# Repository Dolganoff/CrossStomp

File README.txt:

Copyright Alexei Dolganov (http://www.dolganoff.com)

Definitions
-----------

Here, "Documentation" means schematic diagrams, designs, circuit or circuit
board layouts, mechanical drawings, flow charts and descriptive text,
and other explanatory material.

Legal stuff
-----------

This documentation describes Open Hardware product and is licensed under the
CERN OHL 1.2 (see files LICENSE and cern_ohl_v_1_2_howto-1.pdf for more details 
on designs usage and redistribution.

You may redistribute and modify this documentation under the terms of the
CERN OHL 1.2. (http://ohwr.org/cernohl). 

This documentation is distributed WITHOUT ANY EXPRESS OR IMPLIED WARRANTY, 
INCLUDING OF MERCHANTABILITY, SATISFACTORY QUALITY AND FITNESS FOR A 
PARTICULAR PURPOSE. Please see the CERN OHL v.1.2 for applicable conditions.

You're allowed to use this documentation for free and to build the described 
product and even commercialise it **as long as you comply with the license**.
You must redistribute the documentaion with your product under the same
license terms. 

Notification
------------

You're not obliged to do so but I ask you to let me know if you're building
described product for your own use or commercialise it. 

Software tools used in this project:
------------------------------------

* LTSpice (http://www.linear.com/ltspice) - circuit simulations 
  (source files: *.asc)
  LTSpice is a closed source tool but provided free of charge by Linear.  
* Kicad (http://www.kicad-pcb.org) - EDA design tool - schematics capture, PCB 
  production. Any Kicad version   superior to BZR-5000 can be used to open the 
  designs. Kicad is free and available as open source under GPL v2 license.

Folder Structure
----------------

* If you've downloaded this documentation as a zip package, you'll
see the following folders inside:

root: 
  README.txt: this file  
  LICENSE.txt: license terms  
  cern_ohl_v_1_2_howto-1.pdf: guide on licence usage  
  TODO.txt: for unfinished projects only - current project status and todo list.

src:
  documentation sources including schematics, pcb layout and fabrication plots

src/simulations: 
  circuit simulations

src/kicad-tth: 
  kicad project and fab plots for the pedal, traditional leaded "through the hole" components

src/kicad-smd: 
  kicad project and fab plots for the pedal, surface mount components

* If you've obtained this documentation from github repositoty, you'll
see few additional folders:

download:
  latest download zip package

old_do_not_use:
  old files, do not use these ;)

scripts:
  package creation scripts
  
Fabrication files
-----------------

I include standard Gerber files in src/kicad*/plots/plots.zip package
You can send these directly to pcb manufacturer for production. The package
was tested with oshpark and itead, other fab houses may ask for different file
names or formats.

Contact
-------

For all the questions, please contact me (Alexei Dolganov, the author) at 
http://www.dolganoff.com/fr/a-propos/ or message my facebook page
https://www.facebook.com/pages/Dolganoff-Makes-Things/1474869009403564?sk=info

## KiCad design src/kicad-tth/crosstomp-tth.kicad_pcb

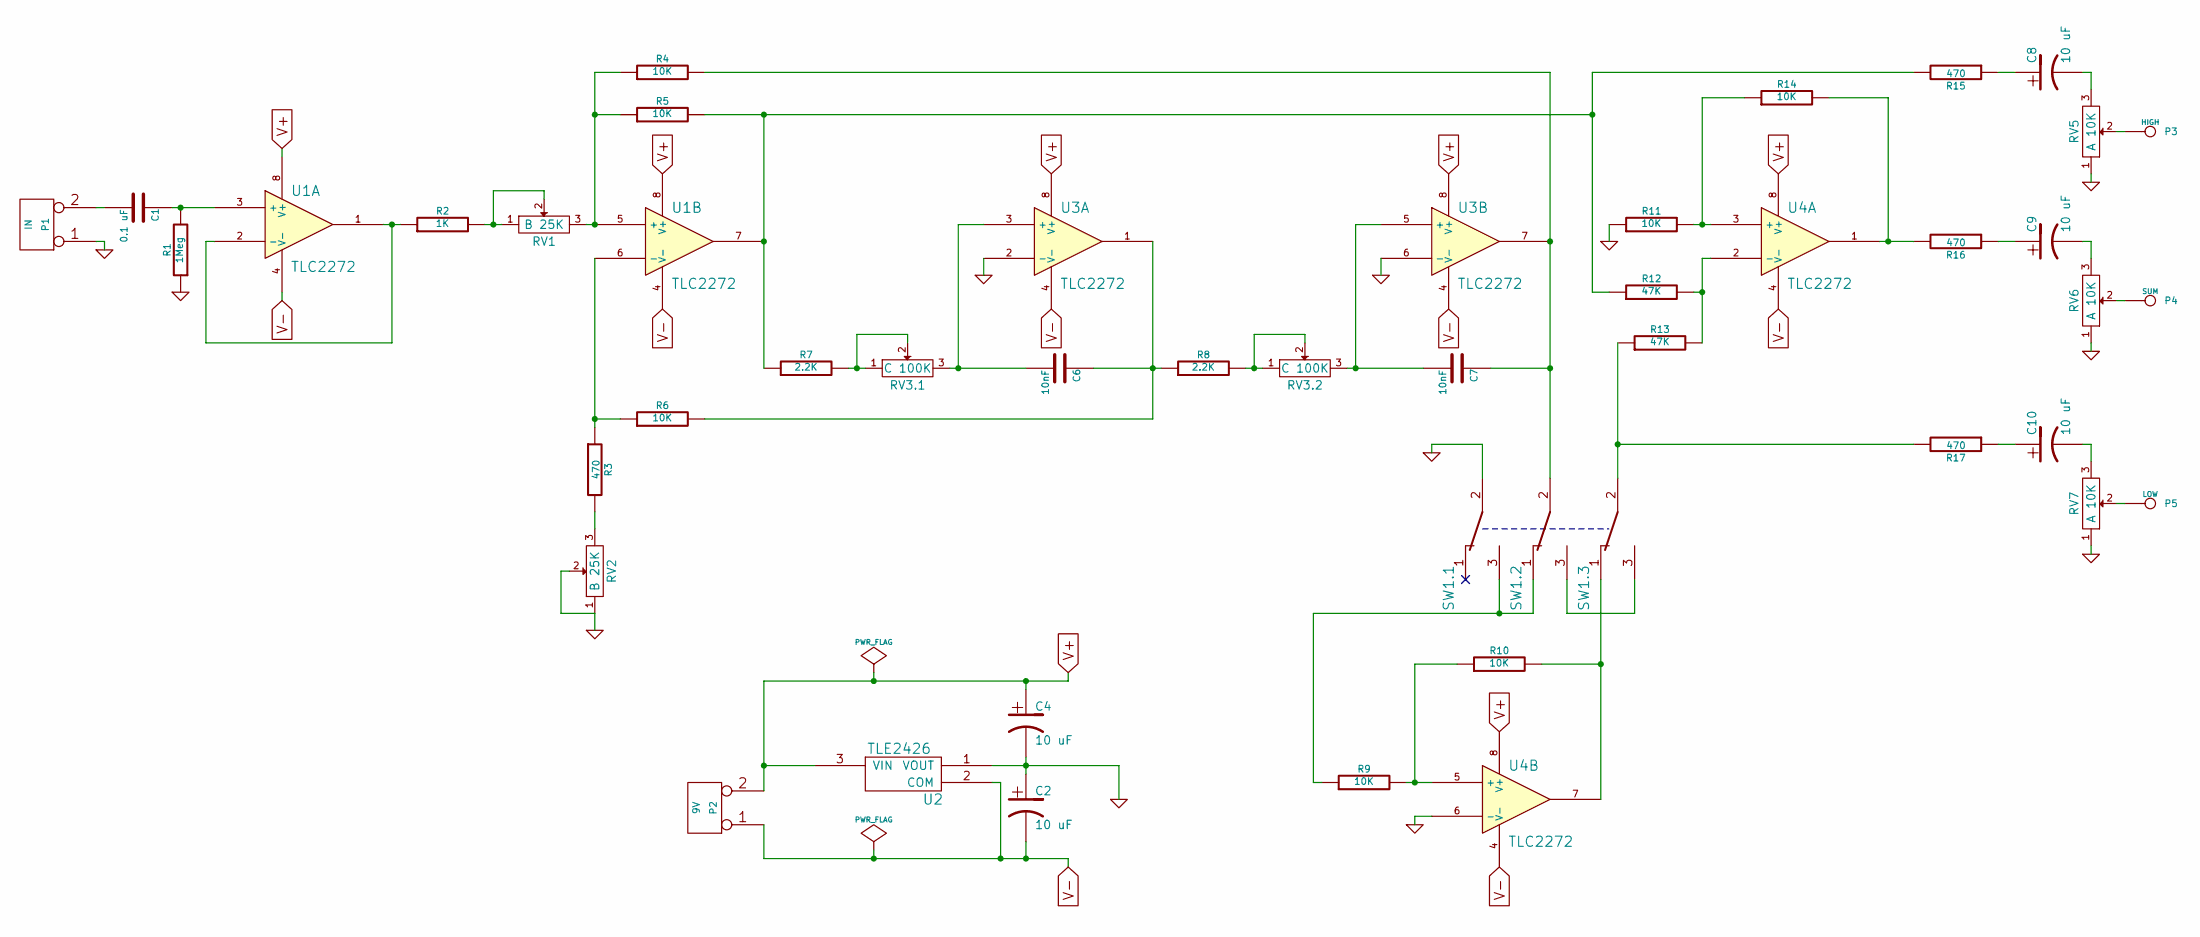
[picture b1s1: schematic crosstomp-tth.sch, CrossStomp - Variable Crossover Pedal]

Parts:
C1: 0.1 uF; C2-LARGE_PADS
C2, C4, C8, C9, C10: 10 uF; C1V5-LARGE_PADS
C6, C7: 10nF; C2-LARGE_PADS
P1: IN; Pin_Header_Straight_1x02
P2: 9V; Pin_Header_Straight_1x02
P3: HIGH; Pin_Header_Straight_1x01
P4: SUM; Pin_Header_Straight_1x01
P5: LOW; Pin_Header_Straight_1x01
R1: 1Meg; R3-LARGE_PADS
R2: 1K; R3-LARGE_PADS
R3, R15, R16, R17: 470; R3-LARGE_PADS
R4, R5, R6, R9, R10, R11, R14: 10K; R3-LARGE_PADS
R7, R8: 2.2K; R3-LARGE_PADS
R12, R13: 47K; R3-LARGE_PADS
RV1, RV2: B 25K; Pin_Header_Straight_1x03
RV3.1, RV3.2: C 100K; Pin_Header_Straight_1x03
RV5, RV6, RV7: A 10K; Pin_Header_Straight_1x03
SW1.1, SW1.2, SW1.3: SW-SPDT; Pin_Header_Straight_1x03
U1, U3, U4: TLC2272; DIP-8_LARGE_PADS
U2: TLE2426; TO-92-Free-rugged

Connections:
GND: C2.1, C4.2, P1.1, R1.1, R11.1, RV2.1, RV2.2, RV5.1, RV6.1, RV7.1, SW1.1.2, U2.1 (VOUT), U3.2 (-), U3.6 (-), U4.6 (-)
unnamed: C1.1, R1.2, U1.3 (+)
unnamed: C1.2, P1.2 (PM)
unnamed: C6.1, R6.2, R8.1, U3.1
unnamed: C6.2, RV3.1.3, U3.3 (+)
unnamed: C7.1, R4.2, SW1.2.2, U3.7
unnamed: C7.2, RV3.2.3, U3.5 (+)
unnamed: C8.1, R15.1
unnamed: C8.2, RV5.3
unnamed: C9.1, R16.1
unnamed: C9.2, RV6.3
unnamed: C10.1, R17.1
unnamed: C10.2, RV7.3
unnamed: P3.1, RV5.2
unnamed: P4.1, RV6.2
unnamed: P5.1, RV7.2
unnamed: R2.1, U1.1, U1.2 (-)
unnamed: R2.2, RV1.1, RV1.2
unnamed: R3.1, R6.1, U1.6 (-)
unnamed: R3.2, RV2.3
unnamed: R4.1, R5.1, RV1.3, U1.5 (+)
unnamed: R7.2, RV3.1.1, RV3.1.2
unnamed: R8.2, RV3.2.1, RV3.2.2
unnamed: R9.1, SW1.1.3, SW1.2.1
unnamed: R9.2, R10.1, U4.5 (+)
unnamed: R10.2, SW1.3.1, U4.7
unnamed: R11.2, R14.1, U4.3 (+)
unnamed: R5.2, R7.1, R12.1, R15.2, U1.7
unnamed: R12.2, R13.2, U4.2 (-)
unnamed: R13.1, R17.2, SW1.3.2
unnamed: R14.2, R16.2, U4.1
unnamed: SW1.2.3, SW1.3.3
V+: C4.1, P2.2 (PM), U1.8 (V+), U2.3 (VIN), U3.8 (V+), U4.8 (V+)
V-: C2.2, P2.1, U1.4 (V-), U2.2 (COM), U3.4 (V-), U4.4 (V-)

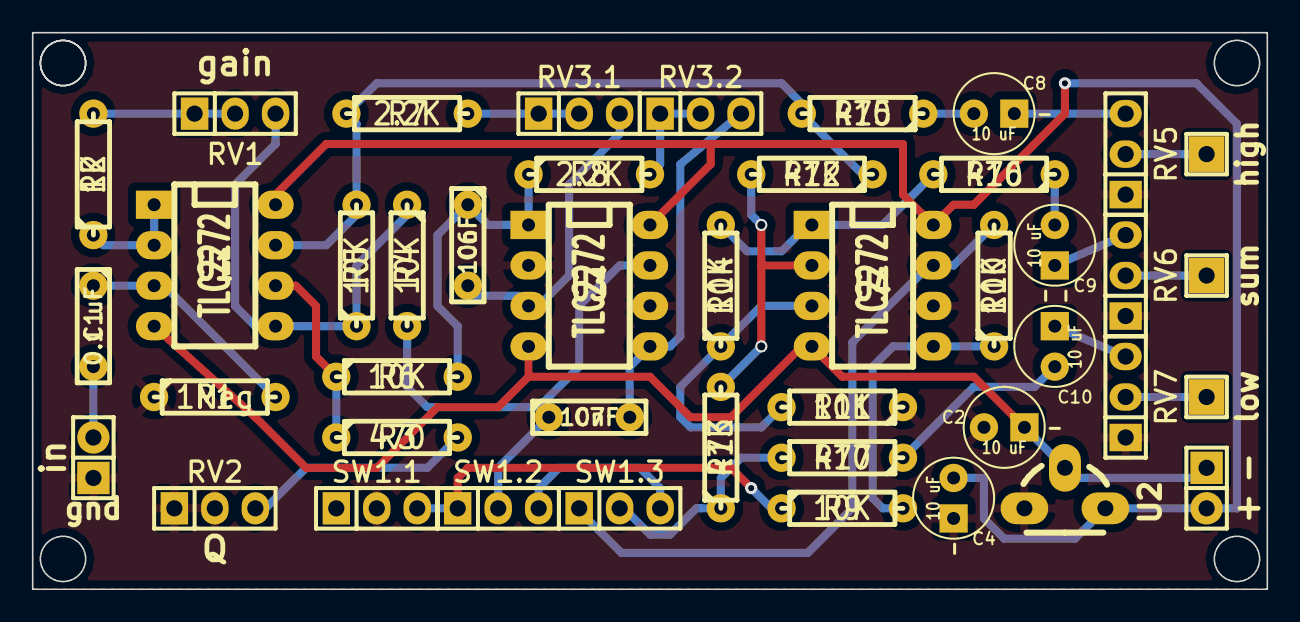
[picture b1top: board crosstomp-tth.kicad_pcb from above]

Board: 2 copper layers, 77.5 x 34.9 mm, 44 parts (0 on the bottom side), 34 nets.

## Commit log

2014-10-12 2014-10-12 initial commit
2014-10-12 readme and todo files modified
2015-01-11 minor upd
2015-04-04 gbr plots

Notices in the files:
src/kicad-tth/crosstomp-tth.kicad_pcb:
Open Hardware, licensed under CERN OHL v1.2.
